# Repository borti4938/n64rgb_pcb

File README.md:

N64RGBv2.1 (PCB)
---

This repository contains all you need files to build your own DIY N64RGBv2.1 board.
Firmware is supplied in another repository.

Please don't ask me for selling a modding.
I either sell some prototypes on some forums marketplaces (which is very unlikely) or I don't have any of the boards.
This is a complete DIY modding project.
Everybody is on his own here.

**WARNING:**
This is an advanced DIY project if you do everything on your own. You need decent soldering skills.
The CPLD and the video DAC have 0.5mm fine pitched pins.
On the board there are some SMD1206 resistor and ferrite bead arrays.
However, there are some awesome shops out there selling the boards for a great price.

## Table of Contents

- [Checklist](https://github.com/borti4938/n64rgb_pcb#checklist-how-to-build-the-project)
- [Assembly](https://github.com/borti4938/n64rgb_pcb#assembly)
- [Installation](https://github.com/borti4938/n64rgb_pcb#installation)
  - [1. Open the Console](https://github.com/borti4938/n64rgb_pcb#1-open-the-console)
  - [2. Optional Steps](https://github.com/borti4938/n64rgb_pcb#2-optional-steps)
  - [3. Solder Work](https://github.com/borti4938/n64rgb_pcb#3-solder-work)
  - [4. Mount the N64 Advanced Modding PCB](https://github.com/borti4938/n64rgb_pcb#4-mount-the-n64-advanced-modding-pcb)
  - [5. Finish the Work](https://github.com/borti4938/n64rgb_pcb#5-finish-the-work)
- [Jumper Setup](https://github.com/borti4938/n64rgb_pcb#jumper-setup)
- [Cable Setup](https://github.com/borti4938/n64rgb_pcb#cable-setup)

## Checklist: How to build the project

- Use PCB files (either [KiCad-PCB design file](./n64rgbv2.1.kicad_pcb) or [Gerber files](./Gerber/)) to order your own PCB or simply use the [shared project(s) on OSHPark](https://oshpark.com/profiles/borti4938)
- If you paln to use solder paste, do not forget to order a stencil for top and bottom, too
- Source the components you need, e.g. from Mouser or Digikey.  
  The BOM is available in [here](./doc/BOM_n64rgbv2.1.xlsx).
- Wait for everything to arrive
- Assemble your PCB if you haven't use a PCBA service
- Set all jumpers
- Flash the firmware ([firmware releases](https://github.com/borti4938/n64rgb_fw/releases)) to the CPLD after installation (e.g. using an Altera USB Blaster)
  - Use the POF programming file named n64rgbv2\_1\__cpld-device_.pof
  - Using the intelFPGA programmer, JTAG chain is initialized by loading POF file
  - N64 needs to be powered for flashing
  - Power cycle the N64 after flashing
- If you want to go for a clean installation with custom made flexible PCBs, just visit the repository for add ons ([Flex PCB for the digital video interface](https://github.com/borti4938/n64rgb_project_misc/RCP2N64RGB), [Flex PCB for the analog video output](https://github.com/borti4938/n64rgb_project_misc/N64RGB2MoutFilter)

## Assembly

If you have all components available, you can start assembly your board.
The documentation provides assembly sheets ([top](./doc/n64rgb2.1_assembly_sheet_top.pdf) and [bottom](./doc/1_assembly_sheet_bot.pdf), which you can print out.
Together with the [BOM](./doc/BOM_n64rgbv2.1.xlsx) it is just a matter of time and effort to assembly everything.
Alternatively you can also use the [interactive BOM](./doc/ibom.html).

Please note that the assembly (and component sourcing) depends on which kind of CPLD family you use.
Supported are Max II and Max V CLPDs.
- If you use a Max II CPLD, you must use FB3 and leave U4, C41 and C42 unpopulated.
- If you use a Max V CPLD, you must use U4, C41 and C42 and leave FB3 unpopulated.

If you populate J3, which is the JTAG connector, please short the pins such that they are flush at the bottom side.
This reduces the risk to short on of these pins with the heat sink (where the PCB will be mounted).

Using non-clean flux (rosin based) is obviously recommended.
Even though it is "non-clean" I recommend cleaning everything afterwards (just for the visual finish).

Please double check everything for shorts once you finished your work.
Very important is that the power supply trace do not short to GND.
- 3.3V against GND (e.g. at C1 and at C52)
- 1.8V against GND (e.g. at C42)
- 5V against GND (e.g. at C4)

## Installation

Note that installation pictures partially show the N64Advanced board.
Pad design and installation is equivalent.

### 1. Open the console

- Remove Jumper Pak / Expansion Pak
- Remove screws from bottom side of the console  
(needs a 4.5mm gamebit tool)
- Lift top housing
- remove inner screws as marked  
(very last consoles made the heat sink design changed slightly)
- pull out the mainboard
- remove heat sink and RF shield
- **Hint** Now you have the chance to clean up your N64 shell

(image by Zerberus (circuit-board.de user))

### 2. Optional Steps

#### 2.1 Preparation of Top RF Shield

This step is optional.
It helps a) to reduce mechanical stress on the flex cable (if used) and b) ensures maximal distance between digital signals (installation wires or flex cable) and analog signals (MultiOut).

- Locate the tap in the RF shield next to the cartridge slot at the side of the MultiOut.  
(this is the place where the installation wires / flex cable will be routed through)
- option 1: bend the tap away

- option 2: simply cut the tab incl. the small piece up to the step in the RF shield

##### Some explanation on this optional step

Later, the data lines as well as the clock will be routed close to the MultiOut.
The distance between both is a crucial issue as your wires act as interferer.
Hence, having the tap bended might be ok, but it is better to cut some piece of the RF shield away to further increase the distance between MultiOut and data lines

#### GND insulation on the MultiOut

To have a better return path for the digital video lines defined, you may insulate GND from the MultiOut.
This step is only recommended if you have a noisy picture.
It comes with the drawback that a) you have a lot of more effort during installation and b) having a longer return path for the analog audio output as well as for S-Video and Composite Video as GND is later routed over the modding board.

- de-solder the MultiOut connector
- drill out the GND pads
- insulare the drills (e.g. with varnish (flex cable or wire install) or small shrink tubes (only wire installation))
- solder MultiOut back into place

### 3. Solder Work

You have the options to either install everything with casual installation wires or using flex cables.
This is just a trade-off between personal installation effort and price.
Personally, I recommend using the flex cable.

Sections 3.1 and 3.2 assume that you want to use the controller functions, so controller 1 will be connected.
However, this is optional, yet at the flex install the controller pad of the flex cable must not be left open!
Please also note section 3.3, where the installation of mechanical switches is described.

#### 3.1 Using the Flex Cable 

To use this option, you have to have the flex cables as shown at hand.
Note that the picture shows older prototype version.

##### 3.1.1 Digital inputs

Start with the digital side:
- Solder the RCP connector side to the RCP-NUS as shown
  - first pin bottom – 8
  - last pin to – 28
- Connect 3.3V to the flex, e.g. taken from C141
- Connect Ctrl. and reset
  - reset from PIF-NUS pin 27
  - Controller from PIF-NUS pin 16  
  (Make sure that PIF-NUS pin 16 is connected to the middle pin of controller port 1, otherwise search for a suitable connection point)
- bend the flex as marked in a way such that you do not see the shaded area anymore.  
The flex will be routed over the MultiOut.

**Note**: when using the flex of version earlier than _v2022xxyy_ you need to cut the RF shield near the MultiOut as shown in 2.1

##### 3.1.2 Analog outputs

Next up is the analog video flex which will be connected to the MultiOut.
Before you start here, make yourself clear where you want to route sync to.
This depends on whether you want to use sync on luma or sync on composite sync (raw sync) cable.

- Free the sync pin from the MultiOut, which means that you must trace back the copper track from the MultiOut pin and make sure that there is nothing connected to.
  - pin 3 (raw sync cable): usually unconnected. Only connected in earlier NTSC console (-CPU-01 to -CPU-03)
  - pin 7 (luma sync cable): usually connected. Search for a nearby resistor or trace back to the DENC-NUS or MAV-NUS and lift the luma pin. Remove the resistor or lift the pin at the DENC-NUS or MAV-NUS.
- solder the flex on its place of the MultiOut
- close **SJ1** on the flex from
  - middle to 3 if using raw sync
  - middle to 7 if using luma sync
- Note that it is also possible to connect sync pin 9 if you want to use a sync on composite video cable.
  - disconnect composite vide from pin 9 using the back tracing technique
  - solder a small wire from **SJ1** middle pad to pin 9 of the MultiOut

#### 3.2 Using Wires

First you need to work out the digital video signals as well as reset and controller 1. 
Most of the signals needed has to be taken from video processor output; the RCP-NUS.
Next to the RCP-NUS is the video encoder, where several types are used during the variety of N64 designs.
The pinouts are given below.
Basically, we need D0-D6, /DSYNC and /CLK (or VCLK or CLOCK) for the modding board.

(RCP-NUS picture by Marshall; Encoder picture by Viletim)

Next to the video signals, you will need to get power (3.3V and GND), reset and controller 1.
This means you need in total 13 wires.
If you use a ribbon cable, I recommend you to use either a 15 conductor cable (double 3.3V and GND) or a 11 conductor cable and separate 3.3V and GND wires. 

- Locate the video encoder
  - Solder a bunch of wires to the video signal pins D0-D6, /DSYNC and /CLK
- Solder wires for reset and controller 1
  - reset from PIF-NUS pin 27
  - Controller from PIF-NUS pin 16  
  (Make sure that PIF-NUS pin 16 is connected to the middle pin of controller port 1, otherwise search for a suitable connection point)
- Solder two additional wires for 3.3V (can be picked off C141) and one for GND (large GND plane)
- Route all wires to the MultiOut port

Next you can prepare wires for the analog video.
Connect several wires to the MultiOut.
Before you start here, make yourself clear where you want to route sync to.
This depends on whether you want to use a sync on composite video, a sync on luma or a sync on composite sync (raw sync) cable.

- Free the sync pin from the MultiOut, which means that you have to trace back the copper track from the MultiOut pin and make sure that there is nothing connected to.
  - pin 3 (raw sync cable): usually unconnected. Only connected in earlier NTSC console (-CPU-01 to -CPU-03)
  - pin 7 (luma sync cable): usually connected. Search for a nearby resistor or trace back to the DENC-NUS or MAV-NUS and lift the luma pin. Remove the resistor or lift the pin at the DENC-NUS or MAV-NUS.
  - pin 9 (composite video sync cable): usually connected. Search for a nearby resistor or trace back to the DENC-NUS or MAV-NUS and lift the luma pin. Remove the resistor or lift the pin at the DENC-NUS or MAV-NUS.
- Prepare some wires to the following pins
  - pin 1: red
  - pin 2: green
  - pin 4: blue
  - pin 3, 7 or 9: sync
  - pin 5 and/or 6: GND (connect pin 5 **and** pin 6 if you insulated GND from the MultiOut)
  - pin 10: 5V

You have the option to use the [Filter AddOn board](https://github.com/borti4938/n64rgb_project_misc/tree/master/FilterAddOn) here.
Note that the filter is optionally included in on the flex cable setup.

If you use the filter board, you clearly have to solder the filter board first and connect the wire to the pads of the filter board as marked on the silk screen.

#### 3.3 Mechanical switch

You can install mechanical switches to toggle VI-DeBlur on and off and also 16bit mode on and off.
At least I recommend installing a mechanical switch for the VI-DeBlur function.

Source a on/on or on/off switch like [this one](https://etim.net.au/shop/shop.php?crn=209&rn=559&action=show_detail).
If you source the switch as linked you can use [this 3D mount](https://www.thingiverse.com/thing:4584239) for a clean installation.

Connect the switch to J11.1 (VI-DeBlur) and/or to J11.2 (16bit mode) in a way such that the switch leaves the jumper open in one position and closes it at the other position.

### 4. Mount the N64 Advanced Modding PCB

The PCB is designed to fit on the heat sink of the N64.
There is a large via on the PCB where a M3 screw passes through.
Mount the PCB using a M3 screw of length 10mm or 12mm, a set of washers and a nut.
Be careful with the JTAG connector **J3** and ensure that the pins do not short to the heatsink!

If you want to use the heat sink shield as an additional secure GND connection, you can also apply some solder to the mounting via.

If everything is mounted and secured, the PCB should sit like that.

### 5. Finish the Work

Before continuing you can assemble the RF shield and heat sink back to the N64 mainboard.
In that way everything is secured in place where it belongs to.
Of course, if you use an installation with wires, make sure that you know which wire is for what.
On my ealrier installs I used some wire marker.

#### 5.1 With Flex Cable

Bend the flex cables gently at the shaded areas.
In that way you should be able to allign both flex cables at the N64RGBv2.1 modding board.
Solder the flex cables at their places.
(Please note subsection 5.3 - CSYNC).

Connect an extra GND wire as shown in 5.3.

#### 5.2 With Wires

Just connect every wire at its place.
The silk screen shows you where everything goes to.
(Please note subsection 5.3 - CSYNC).
Note that the picture shows an older version of the N64 Advanced.
Newer versions have reset and controller at the left-hand side.

Connect an extra GND wire as shown in 5.4.

#### 5.3 CSYNC

You have the option to connect _/CS_ or _/CS (75ohm)_.
I recommend using _/CS (75ohm)_ except if you have a true TTL sink, which is usually not the case!
In virtually 99% of all setups connecting the sync wire to _/CS (75ohm)_ is the way to go.

On installations with the flex cables follows that you must close SJ3 bottom on the flex.
Please note the Jumper Setup section to correctly setup the sync level.

#### 5.4 Extra GND Wire

Connect an extra GND wire to the heat sink screw.
This improves return path properties of the digital video lines.

## Jumper Setup

Jumpers with three pads have _J1#.1_ and _J1#.2_, where .1 is marked with an _arrow_.
Closing either jumper means that a short to the middle pad is needed.

#### J11 (VI-DeBlur and 16bit mode)

This jumper can act as a power cycle default.
You can also switch the state of the jumper using a mechanical switch to toggle the functions during runtime.

##### J11.1 
- opened: VI-DeBlur off
- closed: VI-DeBlur on

##### J11.2
- opened: 16bit mode off
- closed: 16bit mode on

#### J12 (IGR function control)
##### J12.1 (VI-DeBlur and 16bit mode)
- opened: controller functions for toggle VI-DeBlur and 16bit mode on/off are enabled
- closed: controller functions are disabled

##### J12.2 (in game reset)
- opened: reset by controller enabled
- closed: reset by controller disabled

#### J2 (Filter setup)
Needs filter add on to be installed.

- opened: use low pass filter
- closed: bypass filter

#### J21 (Sync on Green)
- open: SoG disabled
- closed: SoG enabled

#### J31 (CSYNC level @ _/CS (75ohm)_ pad)

- opened: appr. 1.87V @ 75ohm termination, i.e. needs a resistor inside the sync wire further attenuating the signal. Designed to work for cables with 470 ohm resistor inside resulting in appr. 450mV @ 75ohm termination
- closed: appr. 300mV @ 75ohm termination suitable for pass through wired cables at sync, works with standard TV / scaler setup

#### J3
_J3_ is the JTAG connector.

## Cable Setup

| Signal | Pin MultiOut | Pin SCART | Ref. GND in SCART | Cinch Plug | Note |
|:-------|:-------------|:----------|:------------------|:-----------|:-----|
| Red / Pr | 1 | 15 | 13 | Red plug | Using a 220uF cap in series is possible, yet not required |
| Green / Y | 2 | 11 | 9 | Green plug | Using a 220uF cap in series is possible, yet not required |
| Blue / Pb | 4 | 7 | 5 | Blue plug | Using a 220uF cap in series is possible, yet not required |
| Sync | 3, 7 or 9 | 20 | 17 | _not needed_ | Pin: See installation, Cable: see notes below |
| GND | 5, 6 | 4,5,9,13,17,18,21 | | Outer ring of each plug | Pin 21 @ SCART: outer shield |
| +5V | 10 | 16 | 18 | _not needed_ | SCART: use a 180ohm resistor in series |
| Audio left | 11 | 6 | 4 | Red plug | |
| Audio right | 12 | 2 | 4 | White plug | |

#### Notes on Sync:

- I recommend using the 75ohm compatible csync output.  
  You have a modding board with J31, you can select with J31 whether
  - you have a series resistor in you cable (J31 open) or
  - if you have a straightly wired sync connection (J31 closed).
- If you use TTL sync output, you have to add an additional resistor in series in every case if you want to use the cable on a non-TTL setup (0ohm to 900ohm) to attenuate the signal for  sinks with 75ohm.

#### RGB cables:

- If you buy an RGB cable, buy a typical RGB cable for a NTSC SNES with sync on luma (MultiAV pin 7) or sync on csync (MultiAV pin 3).
- If you bought a raw csync cable and if you use the 75ohm output, please ensure to set J31 correctly
  
#### PAL RGB cables (SNES PAL):

- PAL RGB cable, i.e. a cable with additional 75ohm resistors to GND, are not supported out of the box.
- You can support them if and only if you have the _Filter AddOn_.  
  To support the cable, replace RN2 with a 39ohm resistor array or solder a second 75ohm resistor array on top of the existing one.

#### RGsB Cables (Cinch):

With the given table you should be able to build your own component cable (passing RGB) or to build an adapter (see pictures below)
Unfortunately, there are no cables / adapter to buy.
Only chance is to buy a Wii component cable and use a MultiOut adapter (SNES/N64/GC style to Wii style).

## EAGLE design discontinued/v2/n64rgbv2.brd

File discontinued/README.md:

### Jumpers N64RGBv1

- J11.1 -> activates 15bit color mode if closed.  **[1]**
- J11.2 -> activates VI-deblur if closed. **[1]**
  - J11.x are just pins on older versions. J11.1 is pin 91 (short to pin 90 to close jumper) and J11.2 is pin 2 (short to pin 1 to close jumper) **[2]**
- Pin 36 -> disables IGR functions toggle deblur and 15bit mode if shorted to pin 37 **[2]**
- J12 -> disables IGR function reset by controller
  - is just pin 66 on older v1 boards without a jumper - short to pin 67 to close jumper **[2]**
- Pad _FIL_ -> einables SD filter from THS7374 if open and disables filter if shorted to GND
  - on older boards it is pin 85 (unfortunately there is no GND pin next to it, so you have to short it with a wire to GND if you need to disable the SD filter)

### Jumpers N64RGBv2

- J11.1 -> activates 15bit color mode if closed.  **[1]**
- J11.2 -> activates VI-deblur if closed. **[1]**
- J12.x -> disables IGR functions if closed
  - x.1: VI-DeBlur and 15bit mode toggle by controller
  - x.2: reset by controller
- J21 -> enables Sync on Green if closed

### Notes  

All pins referring to pins of the CPLD (U1).

**[1]**  
Jumper becomes active on power cycle or if toggled while running operation.  

**[2]**
These are 'hidden jumper', which means it is just a pin where the neighbored pin is GND.

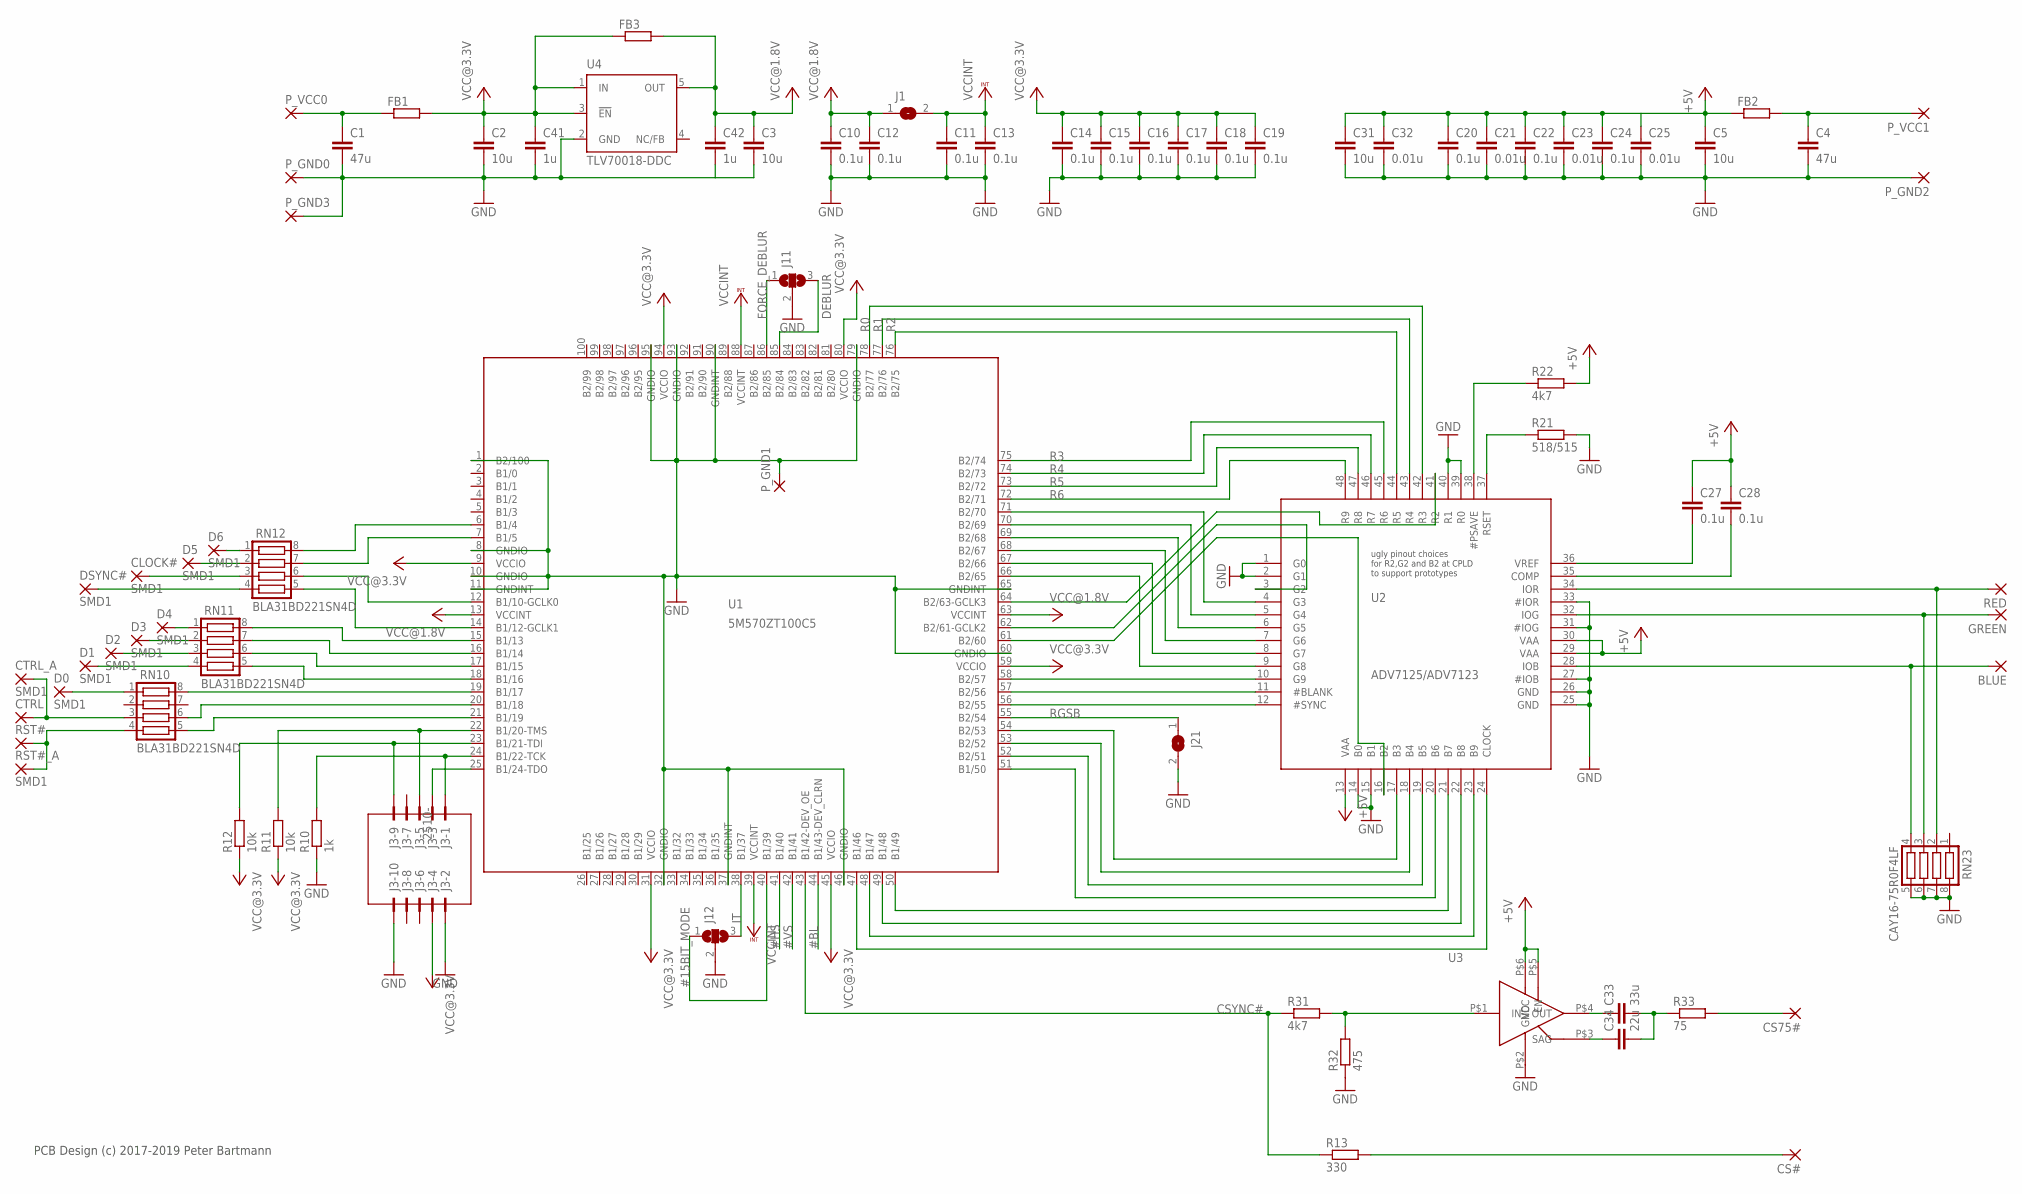
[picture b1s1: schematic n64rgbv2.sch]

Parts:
BLUE: SMD2; SMD1,27-2,54
C1, C4: 47u; C0805
C2, C3, C5, C31: 10u; C0805
C10, C11, C12, C13, C14, C15, C16, C17, C18, C19, C20, C22, C24, C27, C28: 0.1u; C0603
C21, C23, C25, C32: 0.01u; C0603
C33: 33u; C1210
C34: 22u; C1206
C41, C42: 1u; C0603
CLOCK#: SMD1; SMD0,8-1,6
CS75#: SMD2; SMD1,27-2,54
CS#: SMD2; SMD1,27-2,54
CTRL: SMD2; SMD1,27-2,54
CTRL_A: SMD1; SMD0,8-1,6
D0, D1, D2, D3, D4, D5, D6: SMD1; SMD0,8-1,6
DSYNC#: SMD1; SMD0,8-1,6
FB1, FB2, FB3: R-EU_R0603; R0603
GREEN: SMD2; SMD1,27-2,54
J1, J21: SJ
J3: 2510-; PAK100/2500-10
J11, J12: SJ2W; SJ_2
P_GND0, P_GND1, P_GND2, P_GND3: SMD2; SMD1,27-2,54
P_VCC0, P_VCC1: SMD2; SMD1,27-2,54
R10: 1k; R0603
R11, R12: 10k; R0603
R13: 330; R0603
R21: 518/515; R0603
R22, R31: 4k7; R0603
R32: 475; R0603
R33: 75; R0603
RED: SMD2; SMD1,27-2,54
RN10, RN11, RN12: BLA31BD221SN4D; CTS742C083
RN23: CAY16-75R0F4LF; CTS742C083
RST#: SMD2; SMD1,27-2,54
RST#_A: SMD1; SMD0,8-1,6
U1: 5M570ZT100C5; TQFP100
U2: ADV7125/ADV7123; LQFP48
U3: TSH122ICT; SC70
U4: TLV70018-DDC; SOT23-DBV

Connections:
#15BIT_MODE: J12.1, U1.40 (B1/39)
#BL: U1.44 (B1/43-DEV_CLRN)
#HS: U1.41 (B1/40)
#VS: U1.42 (B1/41)
+5V: C5.1, C20.1, C21.1, C22.1, C23.1, C24.1, C25.1, C27.1, C28.1, C31.1, C32.1, FB2.1, R22.2, U2.13 (VAA), U2.29 (VAA), U2.30 (VAA), U3.P$5 (EN), U3.P$6 (VCC)
BLUE: BLUE.1, RN23.4, U2.28 (IOB)
CSYNC#: R13.1, R31.1, U1.43 (B1/42-DEV_OE)
DEBLUR: J11.3, U1.85 (B2/84)
FORCE_DEBLUR: J11.1, U1.86 (B2/85)
GND: C1.2, C2.2, C3.2, C4.2, C5.2, C10.2, C11.2, C12.2, C13.2, C14.2, C15.2, C16.2, C17.2, C18.2, C19.2, C20.2, C21.2, C22.2, C23.2, C24.2, C25.2, C31.2, C32.2, C41.2, C42.2, J3.2, J3.10, J11.2, J12.2, J21.2, P_GND0.1, P_GND1.1, P_GND2.1, P_GND3.1, R10.1, R21.2, R32.1, RN23.5, RN23.6, RN23.7, RN23.8, U1.1 (B2/100), U1.8 (GNDIO), U1.10 (GNDIO), U1.11 (GNDINT), U1.32 (GNDIO), U1.37 (GNDINT), U1.46 (GNDIO), U1.60 (GNDIO), U1.65 (GNDINT), U1.79 (GNDIO), U1.90 (GNDINT), U1.93 (GNDIO), U1.95 (GNDIO), U2.1 (G0), U2.2 (G1), U2.14 (B0), U2.15 (B1), U2.25 (GND), U2.26 (GND), U2.27 (#IOB), U2.31 (#IOG), U2.33 (#IOR), U2.39 (R0), U2.40 (R1), U3.P$2 (GND), U4.2 (GND)
GREEN: GREEN.1, RN23.3, U2.32 (IOG)
IT: J12.3, U1.38 (B1/37)
unnamed: D6.P$1, RN12.1
unnamed: D5.P$1, RN12.2
unnamed: DSYNC#.P$1, RN12.4
unnamed: CLOCK#.P$1, RN12.3
unnamed: RN10.4, RST#.1, RST#_A.P$1
unnamed: CTRL.1, CTRL_A.P$1, RN10.3
unnamed: D0.P$1, RN10.1
unnamed: RN10.8, U1.19 (B1/17)
unnamed: RN10.6, U1.20 (B1/18)
unnamed: RN10.5, U1.21 (B1/19)
unnamed: RN11.5, U1.18 (B1/16)
unnamed: RN11.6, U1.17 (B1/15)
unnamed: CS#.1, R13.2
unnamed: RN11.7, U1.16 (B1/14)
unnamed: RN11.8, U1.15 (B1/13)
unnamed: D1.P$1, RN11.4
unnamed: D2.P$1, RN11.3
unnamed: D3.P$1, RN11.2
unnamed: D4.P$1, RN11.1
unnamed: RN12.7, U1.7 (B1/5)
unnamed: RN12.8, U1.6 (B1/4)
unnamed: RN12.5, U1.14 (B1/12-GCLK1)
unnamed: RN12.6, U1.12 (B1/10-GCLK0)
unnamed: U1.71 (B2/70), U2.4 (G3)
unnamed: U1.64 (B2/63-GCLK3), U2.41 (R2)
unnamed: U1.70 (B2/69), U2.5 (G4)
unnamed: U1.69 (B2/68), U2.6 (G5)
unnamed: U1.68 (B2/67), U2.7 (G6)
unnamed: U1.67 (B2/66), U2.8 (G7)
unnamed: U1.66 (B2/65), U2.9 (G8)
unnamed: U1.58 (B2/57), U2.10 (G9)
unnamed: U1.56 (B2/55), U2.12 (#SYNC)
unnamed: U1.47 (B1/46), U2.24 (CLOCK)
unnamed: U1.48 (B1/47), U2.23 (B9)
unnamed: U1.49 (B1/48), U2.22 (B8)
unnamed: U1.50 (B1/49), U2.21 (B7)
unnamed: U1.51 (B1/50), U2.20 (B6)
unnamed: U1.52 (B2/51), U2.19 (B5)
unnamed: U1.53 (B2/52), U2.18 (B4)
unnamed: U1.54 (B2/53), U2.17 (B3)
unnamed: U1.62 (B2/61-GCLK2), U2.3 (G2)
unnamed: U1.57 (B2/56), U2.11 (#BLANK)
unnamed: U1.61 (B2/60), U2.16 (B2)
unnamed: C4.1, FB2.2, P_VCC1.1
unnamed: C1.1, FB1.1, P_VCC0.1
unnamed: C33.2, C34.2, R33.1
unnamed: CS75#.1, R33.2
unnamed: C33.1, U3.P$4 (OUT)
unnamed: C34.1, U3.P$3 (SAG)
unnamed: R21.1, U2.37 (RSET)
unnamed: R22.1, U2.38 (#PSAVE)
unnamed: C28.2, U2.35 (COMP)
unnamed: R31.2, R32.2, U3.P$1 (IN)
unnamed: C27.2, U2.36 (VREF)
R0: U1.78 (B2/77), U2.42 (R3)
R1: U1.77 (B2/76), U2.43 (R4)
R2: U1.76 (B2/75), U2.44 (R5)
R3: U1.75 (B2/74), U2.45 (R6)
R4: U1.74 (B2/73), U2.46 (R7)
R5: U1.73 (B2/72), U2.47 (R8)
R6: U1.72 (B2/71), U2.48 (R9)
RED: RED.1, RN23.2, U2.34 (IOR)
RGSB: J21.1, U1.55 (B2/54)
TCK: J3.1, R10.2, U1.24 (B1/22-TCK)
TDI: J3.9, R12.2, U1.23 (B1/21-TDI)
TDO: J3.3, U1.25 (B1/24-TDO)
TMS: J3.5, R11.2, U1.22 (B1/20-TMS)
VCC@1.8V: C3.1, C10.1, C12.1, C42.1, FB3.2, J1.1, U1.13 (VCCINT), U1.63 (VCCINT), U4.5 (OUT)
VCC@3.3V: C2.1, C14.1, C15.1, C16.1, C17.1, C18.1, C19.1, C41.1, FB1.2, FB3.1, J3.4, R11.1, R12.1, U1.9 (VCCIO), U1.31 (VCCIO), U1.45 (VCCIO), U1.59 (VCCIO), U1.80 (VCCIO), U1.94 (VCCIO), U4.1 (IN), U4.3 (!EN)
VCCINT: C11.1, C13.1, J1.2, U1.39 (VCCINT), U1.88 (VCCINT)

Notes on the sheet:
ugly pinout choices for R2,G2 and B2 at CPLD to support prototypes
PCB Design (c) 2017-2019 Peter Bartmann

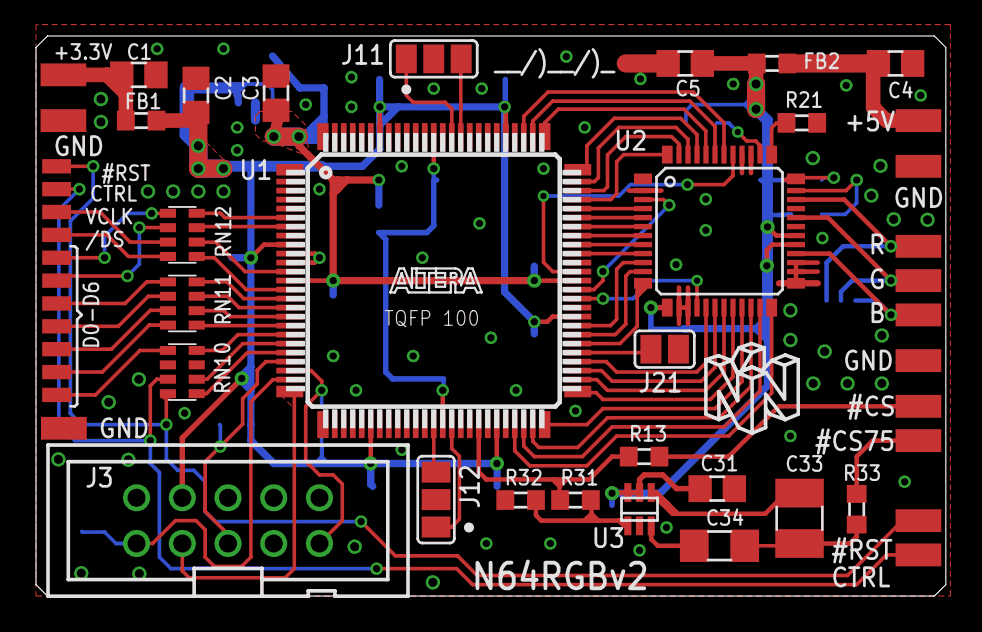
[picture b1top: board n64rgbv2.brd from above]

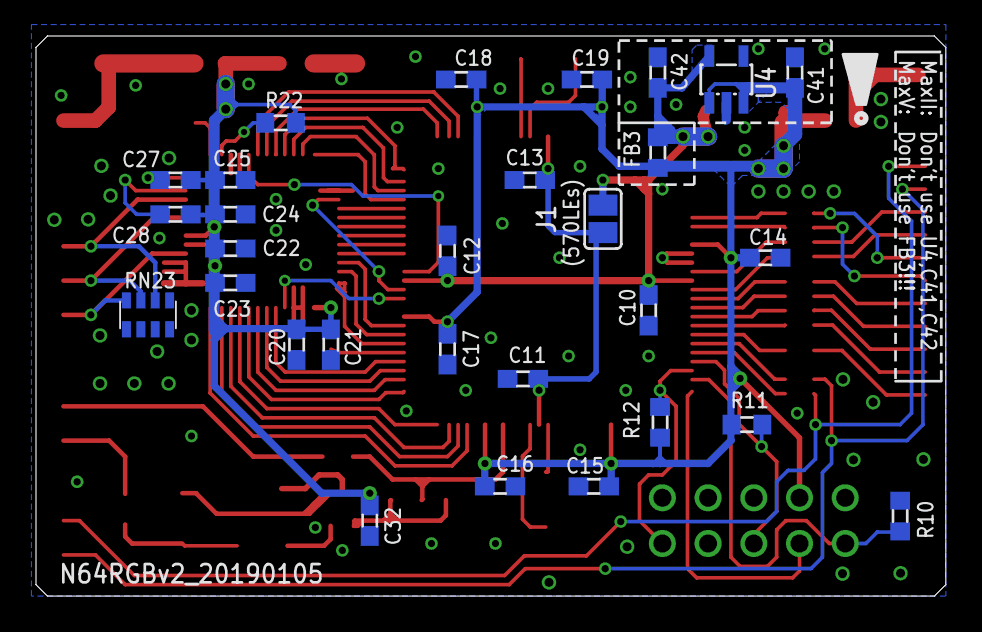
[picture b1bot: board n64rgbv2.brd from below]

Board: 2 copper layers, 50.5 x 31.1 mm, 78 parts (29 on the bottom side), 79 nets.

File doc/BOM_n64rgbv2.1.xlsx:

Number of PCBs |  | 3
Designator | MPN | QTY/PCB | QTY | DESCRIPTION | VALUE | PACKAGE | NOTES
ICs and Regulators
U1 | 5M570ZT100C5N | 1 | 3 | CPLD with 570LEs |  | TQFP100
 | 5M240ZT100C5N |  |  | CPLD with 240LEs |  | TQFP100 | Alternative to 5M570ZT100 with less LEs, leave J1 open
U2 | ADV7125KSTZ50 | 1 | 3 | Video DAC 8bit, 3Ch. |  | 48-LQFP | can be replaced with ADV7123KSTZ50 on demand
U3 | TSH122ICT | 1 | 3 | Video buffer |  | SC-70-6
U4 | TLV70018DDCR | 1 | 3 | 1.8V LDO regulator |  | SOT-23-5
U5 | TLV70033DDCR | 1 | 3 | 3.3V LDO regulator |  | SOT-23-5
Power Supply Filtering
C1,C4 |  | 2 | 6 | Ceramic capacitor, X5R | 47uF / 6.3V | SMD0805
FB1,FB2,FB4,FB5 | BLM18PG471SN1D | 4 | 12 | Ferrit bead |  | SMD0603
Remaining passive components
C2,C3,C5,C6,C31 |  | 5 | 15 | Ceramic capacitor, X5R | 10uF / 6.3V | SMD0805
C10-C19,C20,C22,C24,C27,C28 |  | 15 | 45 | Ceramic capacitor, X7R | 0.1uF / 50V (10%) | SMD0603
C21,C23,C25,C32 |  | 4 | 12 | Ceramic capacitor, X7R | 0.01uF / 50V | SMD0603
C33 |  | 1 | 3 | Ceramic capacitor, X5R | 33uF / 6.3V | SMD0805
C34 |  | 1 | 3 | Ceramic capacitor, X5R | 22uF / 6.3V | SMD0805
C41,C42,C51,C52 |  | 4 | 12 | Ceramic capacitor, X5R | 1uF / 6.3V | SMD0603
R10 | CRCW06031K00FKTB | 1 | 3 | Resistor | 1kohm (1%) | SMD0603
R2,R11, R12 | CRCW0603-10K | 3 | 9 | Resistor | 10kohm (1%) | SMD0603
R13 | RC0603FR-07330RL | 1 | 3 | Resistor | 330ohm (1%) | SMD0603
R21 | RC0603FR-07523RL | 1 | 3 | Resistor | 518 | SMD0603 | with ADV7123: use 516ohm resistor; for PAL-Standard: 528ohm/527ohm
 |  |  |  |  |  |  | Value of MPN reference differs to ideal value to allow for negative margin!
R22,R31 | RC0603FR-074K7L | 2 | 6 | Resistor | 4.7kohm (1%) | SMD0603
R32 | RC0603FR-076K19L | 1 | 3 | Resistor | 6.19kohm (1%) | SMD0603
R33 | RC0603FR-07523RL | 1 | 3 | Resistor | 523 | SMD0603 | usually same as R21
R34 | RC0603FR-0775RL | 1 | 3 | Resistor | 75 | SMD0603
RN10,RN11,RN12 | CAT16-47R0F4LF / CAY16-47R0F4LF | 3 | 9 | Resistor Array (4x) | 47 | SMD1206 | Use this if you don't have resistors at the RCP output or if you use a flex wit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
 | BK32164M121-T |  |  | Ferrite Beads MULTILYR CHP | BD 120OHMS 25% | SMD1206 | Use this alternative if you have resistors at the RCP output, e.g. with the "ol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
RN23 | CAT16-75R0F4LF / CAY16-75R0F4LF |  | 1 | Resistor Array (4x) | 75 | SMD1206
J3 | 30310-6002HB |  | 1 |  |  |  | JTAG Connector
Unpopulated Footprints
FB3 | Don't use FB3 in MaxV setup!!! Otherwise you'll harm your CPLD at first power c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
MPNs are only suggestions! You can use equivalent components, too.

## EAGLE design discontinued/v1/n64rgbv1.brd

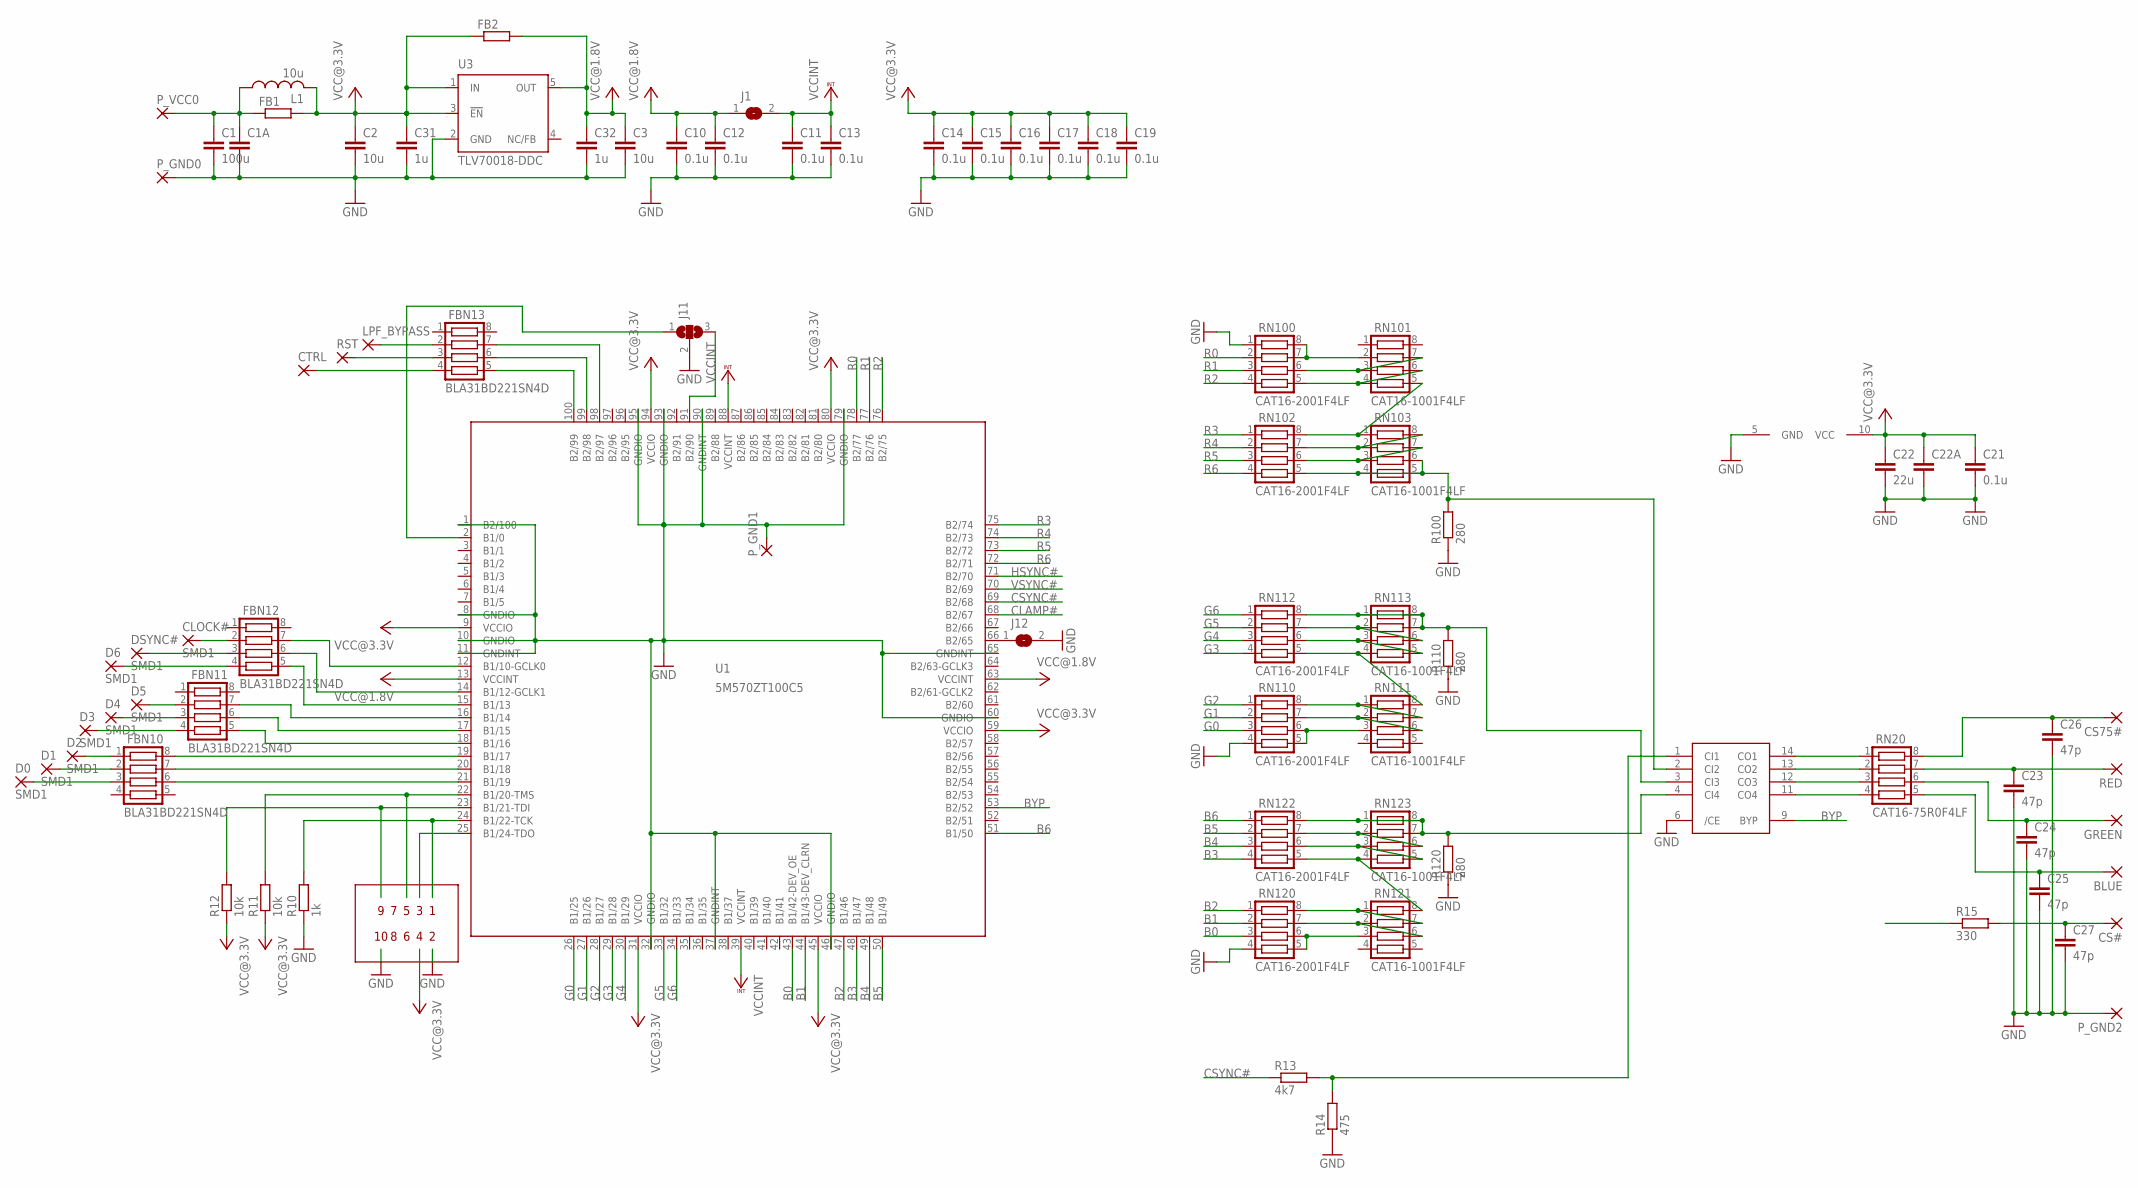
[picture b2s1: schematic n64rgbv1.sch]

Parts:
BLUE: SMD2; SMD1,27-2,54
C1: 100u; C1206K
C1A, C22A: C-EUC0805; C0805
C2, C3: 10u; C0805
C10, C11, C12, C13, C14, C15, C16, C17, C18, C19, C21: 0.1u; C0603
C22: 22u; C1206K
C23, C24, C25, C26, C27: 47p; C0603
C31, C32: 1u; C0603
CLOCK#: SMD1; SMD0,8-1,6
CS75#: SMD2; SMD1,27-2,54
CS#: SMD2; SMD1,27-2,54
CTRL: SMD2; SMD1,27-2,54
D0, D1, D2, D3, D4, D5, D6: SMD1; SMD0,8-1,6
DSYNC#: SMD1; SMD0,8-1,6
FB1, FB2: R-EU_R0603; R0603
FBN10, FBN11, FBN12, FBN13: BLA31BD221SN4D; CTS742C083
GREEN: SMD2; SMD1,27-2,54
J1, J12: SJ
J11: SJ2W; SJ_2
L1: 10u; L3230M
LPF_BYPASS: SMD2; SMD1,27-2,54
P_GND0, P_GND1, P_GND2: SMD2; SMD1,27-2,54
P_VCC0: SMD2; SMD1,27-2,54
R10: 1k; R0603
R11, R12: 10k; R0603
R13: 4k7; R0603
R14: 475; R0603
R15: 330; R0603
R100, R110, R120: 280; R0603
RED: SMD2; SMD1,27-2,54
RN20: CAT16-75R0F4LF; CTS742C083
RN100, RN102, RN110, RN112, RN120, RN122: CAT16-2001F4LF; CTS742C083
RN101, RN103, RN111, RN113, RN121, RN123: CAT16-1001F4LF; CTS742C083
RST: SMD2; SMD1,27-2,54
U1: 5M570ZT100C5; TQFP100
U2: THS7374
U3: TLV70018-DDC; SOT23-DBV

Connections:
B0: RN120.3, U1.43 (B1/42-DEV_OE)
B1: RN120.2, U1.44 (B1/43-DEV_CLRN)
B2: RN120.1, U1.47 (B1/46)
B3: RN122.4, U1.48 (B1/47)
B4: RN122.3, U1.49 (B1/48)
B5: RN122.2, U1.50 (B1/49)
B6: RN122.1, U1.51 (B1/50)
BYP: U1.53 (B2/52), U2.9 (BYP)
CLAMP#: U1.68 (B2/67)
CSYNC#: R13.1, R15.1, U1.69 (B2/68)
G0: RN110.3, U1.26 (B1/25)
G1: RN110.2, U1.27 (B1/26)
G2: RN110.1, U1.28 (B1/27)
G3: RN112.4, U1.29 (B1/28)
G4: RN112.3, U1.30 (B1/29)
G5: RN112.2, U1.33 (B1/32)
G6: RN112.1, U1.34 (B1/33)
GND: C1.2, C1A.2, C2.2, C3.2, C10.2, C11.2, C12.2, C13.2, C14.2, C15.2, C16.2, C17.2, C18.2, C19.2, C21.2, C22.2, C22A.2, C23.2, C24.2, C25.2, C26.2, C27.2, C31.2, C32.2, J11.2, J12.2, P_GND0.1, P_GND1.1, P_GND2.1, R10.1, R14.1, R100.1, R110.1, R120.1, RN100.1, RN110.4, RN120.4, U1.1 (B2/100), U1.8 (GNDIO), U1.10 (GNDIO), U1.11 (GNDINT), U1.32 (GNDIO), U1.37 (GNDINT), U1.46 (GNDIO), U1.60 (GNDIO), U1.65 (GNDINT), U1.79 (GNDIO), U1.90 (GNDINT), U1.93 (GNDIO), U1.95 (GNDIO), U2.5 (GND), U2.6 (/CE), U3.2 (GND)
HSYNC#: U1.71 (B2/70)
unnamed: R13.2, R14.2, U2.1 (CI1)
unnamed: C23.1, RED.1, RN20.7
unnamed: RN20.1, U2.14 (CO1)
unnamed: RN20.2, U2.13 (CO2)
unnamed: RN20.3, U2.12 (CO3)
unnamed: RN20.4, U2.11 (CO4)
unnamed: CTRL.1, FBN13.4
unnamed: FBN13.3, RST.1
unnamed: FBN13.2, LPF_BYPASS.1
unnamed: C24.1, GREEN.1, RN20.6
unnamed: BLUE.1, C25.1, RN20.5
unnamed: C26.1, CS75#.1, RN20.8
unnamed: C27.1, CS#.1, R15.2
unnamed: FBN13.5, U1.100 (B2/99)
unnamed: D1.P$1, FBN10.2
unnamed: D0.P$1, FBN10.3
unnamed: D2.P$1, FBN10.1
unnamed: FBN10.6, U1.21 (B1/19)
unnamed: FBN10.7, U1.20 (B1/18)
unnamed: FBN10.8, U1.19 (B1/17)
unnamed: D3.P$1, FBN11.4
unnamed: D4.P$1, FBN11.3
unnamed: D5.P$1, FBN11.2
unnamed: D6.P$1, FBN12.4
unnamed: RN110.5, RN110.6, RN111.3
unnamed: RN110.7, RN111.2, RN111.6
unnamed: RN110.8, RN111.1, RN111.7
unnamed: RN111.8, RN112.5, RN113.4
unnamed: RN112.6, RN113.3, RN113.5
unnamed: RN112.7, RN113.2, RN113.6
unnamed: R120.2, RN122.8, RN123.1, RN123.7, RN123.8, U2.4 (CI4)
unnamed: RN120.5, RN120.6, RN121.3
unnamed: RN120.7, RN121.2, RN121.6
unnamed: RN120.8, RN121.1, RN121.7
unnamed: RN121.8, RN122.5, RN123.4
unnamed: DSYNC#.P$1, FBN12.3
unnamed: RN122.6, RN123.3, RN123.5
unnamed: RN122.7, RN123.2, RN123.6
unnamed: CLOCK#.P$1, FBN12.2
unnamed: FBN11.5, U1.18 (B1/16)
unnamed: FBN11.6, U1.17 (B1/15)
unnamed: FBN11.7, U1.16 (B1/14)
unnamed: FBN12.5, U1.15 (B1/13)
unnamed: FBN12.6, U1.14 (B1/12-GCLK1)
unnamed: FBN12.7, U1.12 (B1/10-GCLK0)
unnamed: FBN13.6, U1.99 (B2/98)
unnamed: FBN13.7, U1.98 (B2/97)
unnamed: R100.2, RN102.5, RN103.4, RN103.5, RN103.6, U2.2 (CI2)
unnamed: J12.1, U1.66 (B2/65)
unnamed: J11.3, U1.91 (B2/90)
unnamed: J11.1, U1.2 (B1/0)
unnamed: C1.1, C1A.1, FB1.1, L1.1, P_VCC0.1
unnamed: R110.2, RN112.8, RN113.1, RN113.7, RN113.8, U2.3 (CI3)
unnamed: RN100.7, RN100.8, RN101.2
unnamed: RN100.6, RN101.3, RN101.7
unnamed: RN100.5, RN101.4, RN101.6
unnamed: RN101.5, RN102.8, RN103.1
unnamed: RN102.7, RN103.2, RN103.8
unnamed: RN102.6, RN103.3, RN103.7
R0: RN100.2, U1.78 (B2/77)
R1: RN100.3, U1.77 (B2/76)
R2: RN100.4, U1.76 (B2/75)
R3: RN102.1, U1.75 (B2/74)
R4: RN102.2, U1.74 (B2/73)
R5: RN102.3, U1.73 (B2/72)
R6: RN102.4, U1.72 (B2/71)
TCK: R10.2, U1.24 (B1/22-TCK)
TDI: R12.2, U1.23 (B1/21-TDI)
TDO: U1.25 (B1/24-TDO)
TMS: R11.2, U1.22 (B1/20-TMS)
VCC@1.8V: C3.1, C10.1, C12.1, C32.1, FB2.2, J1.1, U1.13 (VCCINT), U1.63 (VCCINT), U3.5 (OUT)
VCC@3.3V: C2.1, C14.1, C15.1, C16.1, C17.1, C18.1, C19.1, C21.1, C22.1, C22A.1, C31.1, FB1.2, FB2.1, L1.2, R11.1, R12.1, U1.9 (VCCIO), U1.31 (VCCIO), U1.45 (VCCIO), U1.59 (VCCIO), U1.80 (VCCIO), U1.94 (VCCIO), U2.10 (VCC), U3.1 (IN), U3.3 (!EN)
VCCINT: C11.1, C13.1, J1.2, U1.39 (VCCINT), U1.88 (VCCINT)
VSYNC#: U1.70 (B2/69)

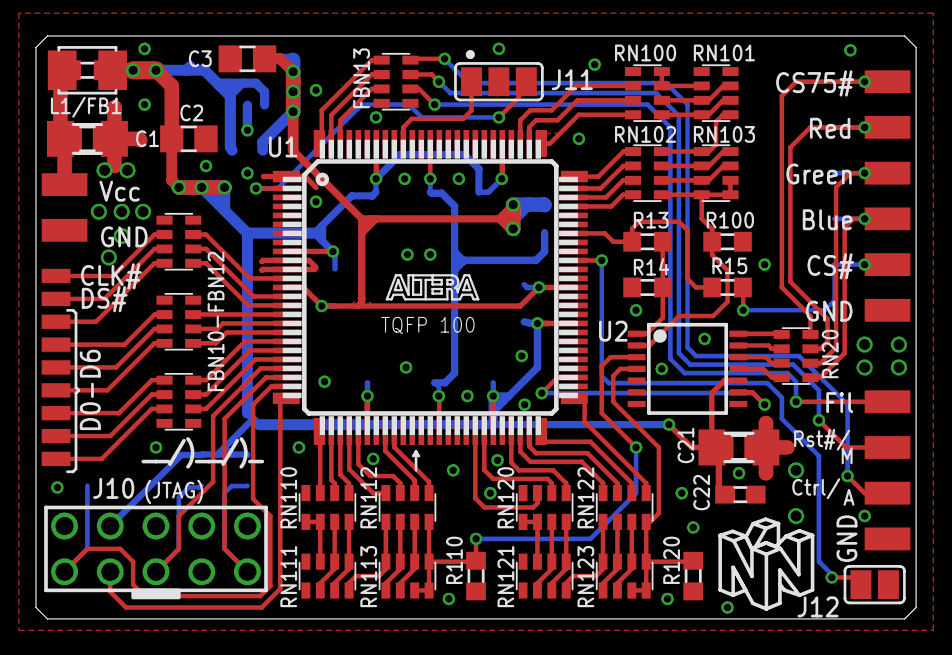
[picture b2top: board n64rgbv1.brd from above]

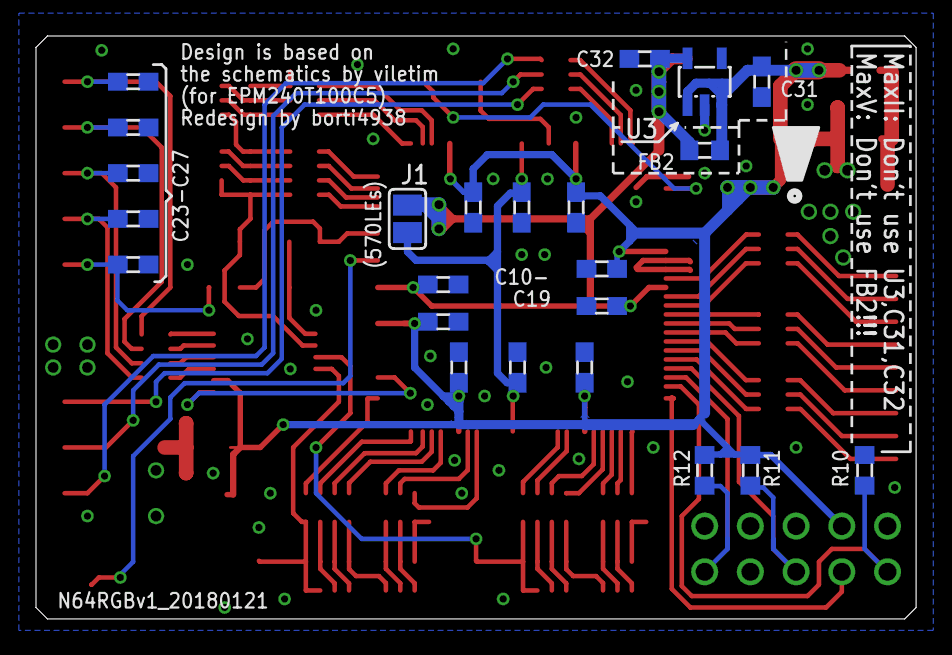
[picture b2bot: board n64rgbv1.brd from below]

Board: 2 copper layers, 48.9 x 32.4 mm, 80 parts (23 on the bottom side), 89 nets.

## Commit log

2022-03-27 add readme
2022-03-27 add table of contents and a remark on MaxII and MaxV assembly differences
2022-03-29 remove some typos, adapt some wording
2022-07-13 typo fix
2022-07-13 misc updates: - update KiCad to v6 - add SMD footprint for JTAG connector
